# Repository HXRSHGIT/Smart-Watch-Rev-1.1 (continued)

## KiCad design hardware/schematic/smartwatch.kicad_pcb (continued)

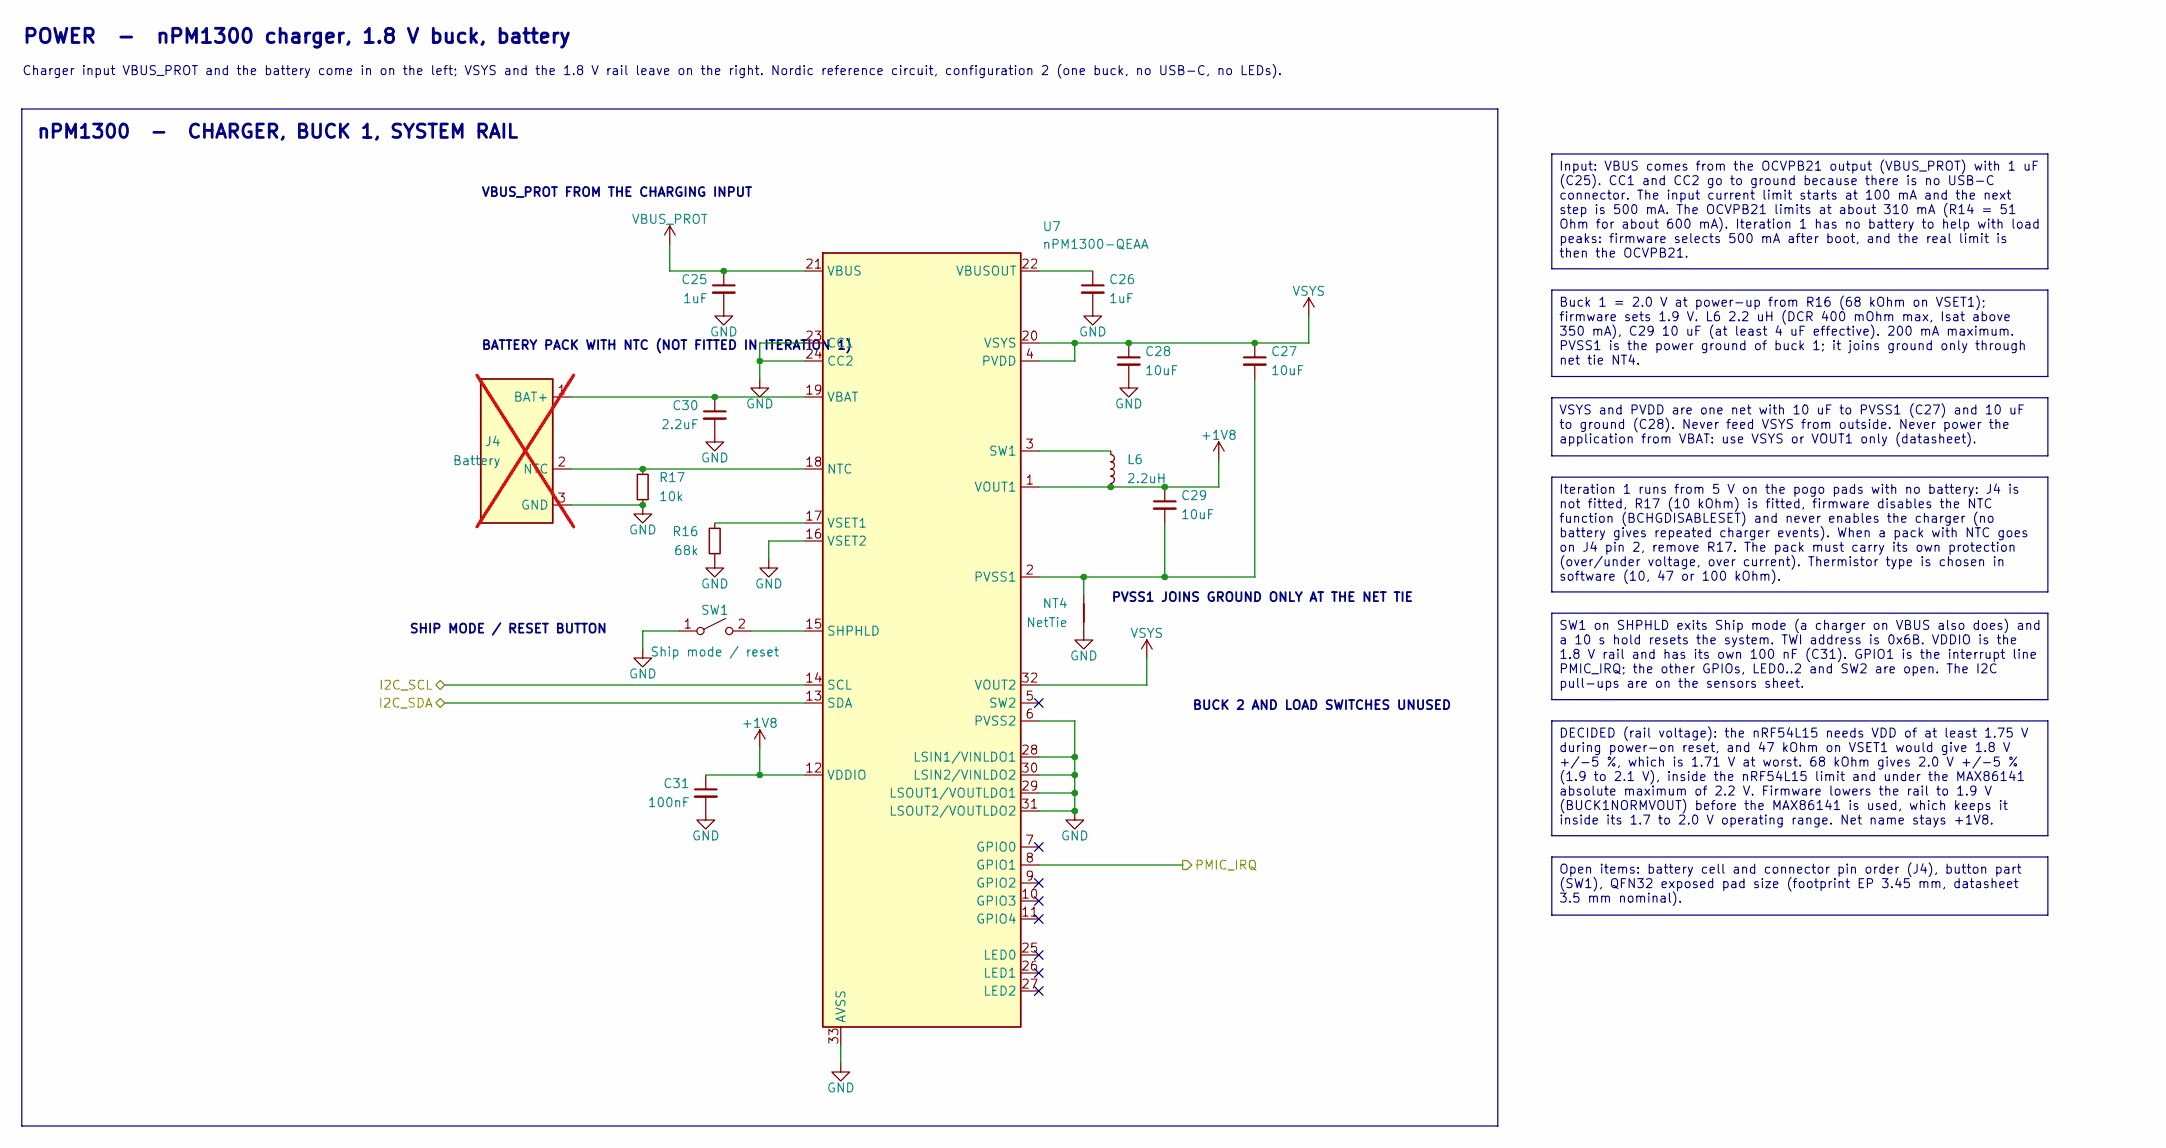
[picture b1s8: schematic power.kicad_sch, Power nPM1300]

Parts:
C25, C26: 1uF; C_0603_1608Metric
C27, C28, C29: 10uF; C_0603_1608Metric
C30: 2.2uF; C_0603_1608Metric
C31: 100nF; C_0201_0603Metric
J4: Battery; JST_SH_SM03B-SRSS-TB_1x03-1MP_P1.00mm_Horizontal; not fitted
L6: 2.2uH; L_0805_2012Metric
NT4: NetTie; NetTie-2_SMD_Pad0.5mm
R16: 68k; R_0201_0603Metric
R17: 10k; R_0201_0603Metric
SW1: Ship mode / reset; SW_SPST_B3U-1000P
U7: nPM1300-QEAA; QFN-32-1EP_5x5mm_P0.5mm_EP3.45x3.45mm

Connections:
+1V8: C29.1, C31.1, L6.2, U7.1 (VOUT1), U7.12 (VDDIO); also elsewhere on the board
/I2C_SCL: U7.14 (SCL); also elsewhere on the board
/I2C_SDA: U7.13 (SDA); also elsewhere on the board
/mcu/PMIC_IRQ: U7.8 (GPIO1); also elsewhere on the board
GND: C25.2, C26.2, C28.2, C30.2, C31.2, J4.3 (GND), NT4.1, R16.2, R17.2, SW1.1 (A), U7.6 (PVSS2), U7.16 (VSET2), U7.23 (CC1), U7.24 (CC2), U7.28 (LSIN1/VINLDO1), U7.29 (LSOUT1/VOUTLDO1), U7.30 (LSIN2/VINLDO2), U7.31 (LSOUT2/VOUTLDO2), U7.33 (AVSS); also elsewhere on the board
unnamed: C30.1, J4.1 (BAT+), U7.19 (VBAT)
unnamed: J4.2 (NTC), R17.1, U7.18 (NTC)
unnamed: SW1.2 (B), U7.15 (SHPHLD)
unnamed: C27.2, C29.2, NT4.2, U7.2 (PVSS1)
unnamed: L6.1, U7.3 (SW1)
unnamed: C26.1, U7.22 (VBUSOUT)
unnamed: R16.1, U7.17 (VSET1)
VBUS_PROT: C25.1, U7.21 (VBUS); also elsewhere on the board
VSYS: C27.1, C28.1, U7.4 (PVDD), U7.20 (VSYS), U7.32 (VOUT2); also elsewhere on the board

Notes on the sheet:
POWER - nPM1300 charger, 1.8 V buck, battery
Charger input VBUS_PROT and the battery come in on the left; VSYS and the 1.8 V rail leave on the right. Nordic reference circuit, configuration 2 (one buck, no USB-C, no LEDs).
nPM1300 - CHARGER, BUCK 1, SYSTEM RAIL
VBUS_PROT FROM THE CHARGING INPUT
BATTERY PACK WITH NTC (NOT FITTED IN ITERATION 1)
SHIP MODE / RESET BUTTON
PVSS1 JOINS GROUND ONLY AT THE NET TIE
BUCK 2 AND LOAD SWITCHES UNUSED
Input: VBUS comes from the OCVPB21 output (VBUS_PROT) with 1 uF (C25). CC1 and CC2 go to ground because there is no USB-C connector. The input current limit starts at 100 mA and the next step is 500 mA. The OCVPB21 limits at about 310 mA (R14 = 51 Ohm for about 600 mA). Iteration 1 has no battery t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
Buck 1 = 2.0 V at power-up from R16 (68 kOhm on VSET1); firmware sets 1.9 V. L6 2.2 uH (DCR 400 mOhm max, Isat above 350 mA), C29 10 uF (at least 4 uF effective). 200 mA maximum. PVSS1 is the power ground of buck 1; it joins ground only through net tie NT4.
VSYS and PVDD are one net with 10 uF to PVSS1 (C27) and 10 uF to ground (C28). Never feed VSYS from outside. Never power the application from VBAT: use VSYS or VOUT1 only (datasheet).
Iteration 1 runs from 5 V on the pogo pads with no battery: J4 is not fitted, R17 (10 kOhm) is fitted, firmware disables the NTC function (BCHGDISABLESET) and never enables the charger (no battery gives repeated charger events). When a pack with NTC goes on J4 pin 2, remove R17. The pack must carry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
SW1 on SHPHLD exits Ship mode (a charger on VBUS also does) and a 10 s hold resets the system. TWI address is 0x6B. VDDIO is the 1.8 V rail and has its own 100 nF (C31). GPIO1 is the interrupt line PMIC_IRQ; the other GPIOs, LED0..2 and SW2 are open. The I2C pull-ups are on the sensors sheet.
DECIDED (rail voltage): the nRF54L15 needs VDD of at least 1.75 V during power-on reset, and 47 kOhm on VSET1 would give 1.8 V +/-5 %, which is 1.71 V at worst. 68 kOhm gives 2.0 V +/-5 % (1.9 to 2.1 V), inside the nRF54L15 limit and under the MAX86141 absolute maximum of 2.2 V. Firmware lowers the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
Open items: battery cell and connector pin order (J4), button part (SW1), QFN32 exposed pad size (footprint EP 3.45 mm, datasheet 3.5 mm nominal).

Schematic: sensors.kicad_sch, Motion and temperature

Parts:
C19, C20, C21: 100nF; C_0201_0603Metric
R9, R10: 4.7k; R_0201_0603Metric
TP6: TP I2C_SDA; TestPoint_Pad_D1.0mm
TP7: TP I2C_SCL; TestPoint_Pad_D1.0mm
U3: BMI270; Bosch_LGA-14_3x2.5mm_P0.5mm
U4: MAX30208; MAX30208_TLGA-10_2x2mm

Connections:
+1V8: C19.1, C20.1, C21.1, R9.1, R10.1, U3.2 (ASDx), U3.3 (ASCx), U3.5 (VDDIO), U3.8 (VDD), U3.12 (CSB), U4.1 (VDD), U4.2 (VDD), U4.3 (VDD); also elsewhere on the board
/I2C_SCL: R9.2, TP7.1, U3.13 (SCx (SCL)), U4.9 (SCL); also elsewhere on the board
/I2C_SDA: R10.2, TP6.1, U3.14 (SDx (SDA)), U4.8 (SDA); also elsewhere on the board
/mcu/IMU_INT1: U3.4 (INT1); also elsewhere on the board
/mcu/IMU_INT2: U3.9 (INT2); also elsewhere on the board
/mcu/TEMP_INT: U4.10 (GPIO0); also elsewhere on the board
GND: C19.2, C20.2, C21.2, U3.1 (SDO), U3.6 (GNDIO), U3.7 (GND), U4.4 (GND), U4.5 (GND), U4.6 (GND), U4.7 (GPIO1); also elsewhere on the board

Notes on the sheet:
MOTION AND SKIN TEMPERATURE - BMI270 + MAX30208 on the I2C bus
Both parts run from the 1.8 V rail and share SDA / SCL. Interrupts go to the processor.
BMI270 - MOTION
I2C PULL-UPS
MAX30208 - SKIN TEMPERATURE
BMI270: I2C address 0x68 because SDO is tied to ground. CSB high selects I2C. ASDx and ASCx (the secondary interface) are tied to VDDIO as the datasheet requires, never to ground. OCSB and OSDO are not used.
C19 and C20 are decoupling capacitors for BMI270 VDD and VDDIO (100 nF each). Keep them close to the pins.
MAX30208: address 0x50. GPIO1 is tied to ground, and GPIO0 reads low at start-up through its internal 1 MOhm pull-down, so the address stays 0x50. GPIO0 is the temperature alarm output (TEMP_INT), open drain and active low in INTB mode: set that mode first, then enable the processor's internal pull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
C21 decouples MAX30208 VDD (100 nF). Keep it close to the pins. Read PCN 2204 before ordering.
One pair of 4.7 kOhm pull-ups serves the whole bus. At 400 kHz and about 50 pF the rise time is about 0.2 us. The nPM1300 joins this bus on the power sheet.

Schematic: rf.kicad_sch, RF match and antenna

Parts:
AE1: 2450AT18A0100001E; Johanson_2450AT18A0100001E_1206
C6: 1.5pF; C_0201_0603Metric; MPN GJM0335C1E1R5WB01
C9: 2.0pF; C_0201_0603Metric; MPN GJM0335C1E2R0WB01
C11: 0.3pF; C_0201_0603Metric
C14: TBD; C_0402_1005Metric; not fitted
L2: 2.7nH; L_0201_0603Metric; MPN LQP03HQ2N7B02
L3, L4: 3.5nH; L_0201_0603Metric; MPN LQP03HQ3N5B02
NT2: NetTie; NetTie-2_SMD_Pad0.5mm
R2, R3: 0R; R_0402_1005Metric

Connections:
/mcu/RF_ANT: L2.1; also elsewhere on the board
/mcu/VSS_PA: C6.2; also elsewhere on the board
GND: C11.2, C14.2, NT2.1; also elsewhere on the board
unnamed: AE1.1 (FEED), R3.2
unnamed: C6.1, L2.2, L3.1
unnamed: C9.1, L3.2, L4.1
unnamed: C9.2, NT2.2
unnamed: C11.1, L4.2, R2.1
unnamed: C14.1, R2.2, R3.1

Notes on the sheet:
RF - Nordic match network, antenna tee, chip antenna
The signal runs left to right: ANT pin of the processor, series-shunt-series filter, tee slots, antenna.
NORDIC FILTER AND MATCH
ANTENNA TEE AND ANTENNA
BOTTOM GND ONLY
Nordic network: C6 returns to VSS_PA on the TOP layer only. C9 returns to the BOTTOM ground layer only (net tie NT2). Place the whole network as close to the ANT pin as possible. (nRF54L15 datasheet, Fig 180 and Table 87)
Antenna tee: 0R, empty, 0R as a start (R2, C14, R3). The antenna is the Johanson 2450AT18A0100001E in a corner with its keep-out. Tune on the worn band with the final housing. Pin 2 is only a solder anchor. Johanson's own evaluation board uses series 1.0 pF, shunt 2.7 nH, series 3.9 nH: the shunt s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

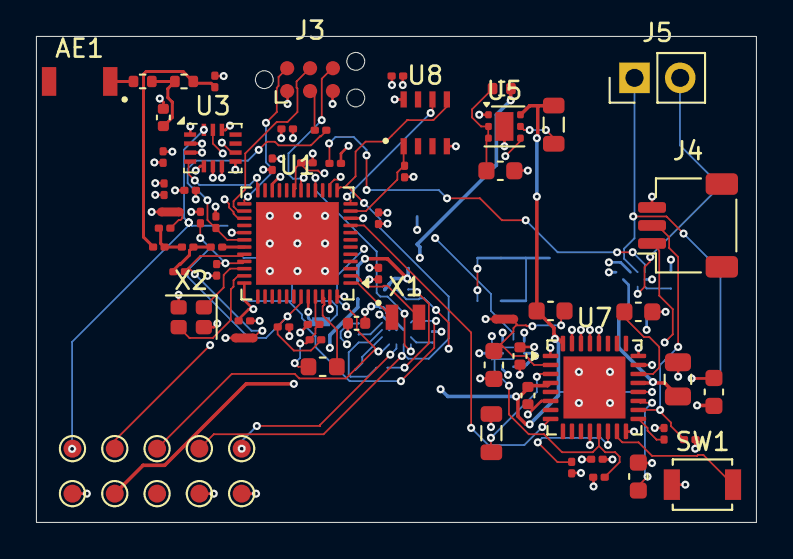
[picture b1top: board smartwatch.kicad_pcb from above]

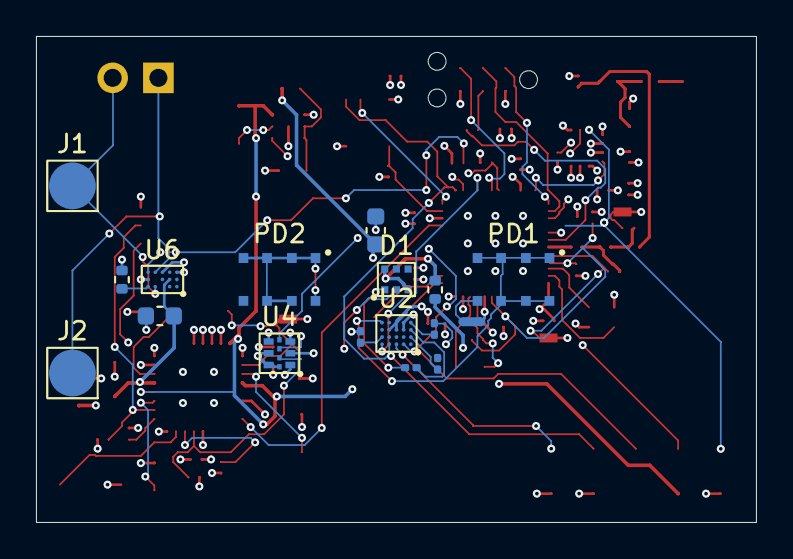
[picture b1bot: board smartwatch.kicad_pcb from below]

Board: 4 copper layers, 40.0 x 27.0 mm, 89 parts (17 on the bottom side), 60 nets.

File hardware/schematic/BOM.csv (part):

Reference,Value,Footprint,Spec,MPN,Source,Note
AE1,2450AT18A0100001E,smartwatch:Johanson_2450AT18A0100001E_1206,,,Johanson DS 36S0021A rev 4.0,
C1,2.2uF,Capacitor_SMD:C_0201_0603Metric,X6T 20% 2.5V,,nRF54L15 DS v1.0 Table 87 / Fig 180,
C2,2.2uF,Capacitor_SMD:C_0201_0603Metric,X6T 20% 2.5V,,nRF54L15 DS v1.0 Table 87 / Fig 180,
C3,10uF,Capacitor_SMD:C_0402_1005Metric,X6S 20% 6.3V,,nRF54L15 DS v1.0 Table 87 / Fig 180,
C4,100nF,Capacitor_SMD:C_0201_0603Metric,X7R 10%,,nRF54L15 DS v1.0 Table 87 / Fig 180,
C5,2.2nF,Capacitor_SMD:C_0201_0603Metric,X7R 10% 10V,,nRF54L15 DS v1.0 Table 87 / Fig 180,
C6,1.5pF,Capacitor_SMD:C_0201_0603Metric,NP0 0.05 pF 25V high Q,GJM0335C1E1R5WB01,nRF54L15 DS v1.0 Fig 180 / Table 87,
C7,100nF,Capacitor_SMD:C_0201_0603Metric,X7R 10%,,nRF54L15 DS v1.0 Table 87 / Fig 180,
C8,100nF,Capacitor_SMD:C_0201_0603Metric,X7R 10%,,nRF54L15 DS v1.0 Table 87 / Fig 180,
C9,2.0pF,Capacitor_SMD:C_0201_0603Metric,NP0 0.05 pF 25V,GJM0335C1E2R0WB01,nRF54L15 DS v1.0 Fig 180 / Table 87,
C10,100nF,Capacitor_SMD:C_0201_0603Metric,X7R 10%,,nRF54L15 DS v1.0 Table 87 / Fig 180,
C11,0.3pF,Capacitor_SMD:C_0201_0603Metric,C0G 0.1 pF 50V,,nRF54L15 DS v1.0 Fig 180 / Table 87,
C12,10nF,Capacitor_SMD:C_0201_0603Metric,X7R 6.3V,,nRF54L15 DS v1.0 Table 87 / Fig 180,
C13,3.9pF,Capacitor_SMD:C_0201_0603Metric,C0G 0.25pF 50V,,nRF54L15 DS v1.0 Table 87 / Fig 180,
C14,TBD,Capacitor_SMD:C_0402_1005Metric,"shunt slot, tune on worn band",,Johanson DS 36S0021A note 4,DNP
C15,22uF,Capacitor_SMD:C_0402_1005Metric,"6.3V or higher, effective ~10 uF",,MAX86141 DS Rev 5 p.49,
C16,100nF,Capacitor_SMD:C_0201_0603Metric,at the VDD_ANA ball,,MAX86141 DS Rev 5 p.12,
C17,1uF,Capacitor_SMD:C_0201_0603Metric,6.3V (VREF is 1.21 V),,MAX86141 DS Rev 5 p.12,
C18,10uF,Capacitor_SMD:C_0603_1608Metric,10V X5R (VLED up to 5.5 V),,MAX86141 DS Rev 5 p.12,
C19,100nF,Capacitor_SMD:C_0201_0603Metric,X7R 10%,,BMI270 DS Rev 08 section 7.2,
C20,100nF,Capacitor_SMD:C_0201_0603Metric,X7R 10%,,BMI270 DS Rev 08 section 7.2,
C21,100nF,Capacitor_SMD:C_0201_0603Metric,X7R 10%,,MAX30208 DS Rev 1 p.5 pin table,
C22,2.2uF,Capacitor_SMD:C_0402_1005Metric,X5R 6.3V min,,TPS61240 DS SLVS806D Table 2,
C23,10uF,Capacitor_SMD:C_0603_1608Metric,X5R 10V (effective >= 2.7 uF at 5 V),,TPS61240 DS SLVS806D 10.2.2.4,
C24,22uF,Capacitor_SMD:C_0805_2012Metric,"X5R 16V low ESR, >= 10 uF effective at 5 V",,OCVPB21-13F6 DS13107 Rev 3 Table 2,
C25,1uF,Capacitor_SMD:C_0603_1608Metric,X5R 10V 10%,,"nPM1300 PS v1.3 Reference circuitry, Configuration 2 C1",
C26,1uF,Capacitor_SMD:C_0603_1608Metric,"X5R 10V 10%, mandatory on VBUSOUT",,"nPM1300 PS v1.3 Reference circuitry, Configuration 2 C5",
C27,10uF,Capacitor_SMD:C_0603_1608Metric,"X5R 25V 20%, returns to PVSS1",,"nPM1300 PS v1.3 Reference circuitry, Configuration 2 C2",
C28,10uF,Capacitor_SMD:C_0603_1608Metric,X5R 25V 20%,,"nPM1300 PS v1.3 Reference circuitry, Configuration 2 C4",
C29,10uF,Capacitor_SMD:C_0603_1608Metric,X5R 25V 20% (>= 4 uF effective),,"nPM1300 PS v1.3 Reference circuitry, Configuration 2 C7",
C30,2.2uF,Capacitor_SMD:C_0603_1608Metric,X7R 16V 10%,,"nPM1300 PS v1.3 Reference circuitry, Configuration 2 C6",
C31,100nF,Capacitor_SMD:C_0201_0603Metric,X5R 10%,,"nPM1300 PS v1.3 Reference circuitry, Configuration 2 C13",
C32,100nF,Capacitor_SMD:C_0201_0603Metric,"X7R 10%, close to the VCC land",,MX25R3235F DS rev 1.6 section 12,
D1,SFH 7016,smartwatch:SFH7016_1.85x1.65mm,,,,
FB1,120R@100MHz,Inductor_SMD:L_0201_0603Metric,200 mA 500 mOhm max,,nRF54L15 DS v1.0 Table 87 / Fig 180,
J1,Pogo pad,smartwatch:Pogo_Pad_D2.6mm,,,research/power-battery/POGO_CHARGING.md,
J2,Pogo pad,smartwatch:Pogo_Pad_D2.6mm,,,research/power-battery/POGO_CHARGING.md,
J3,TC2030-NL,Connector:Tag-Connect_TC2030-IDC-NL_2x03_P1.27mm_Vertical,,,,
J4,Battery,Connector_JST:JST_SH_SM03B-SRSS-TB_1x03-1MP_P1.00mm_Horizontal,not fitted in iteration 1 (no battery),,battery cell and connector: open item,
J5,5 V in,Connector_PinHeader_2.54mm:PinHeader_1x02_P2.54mm_Vertical,,,iteration 1: 5 V input without pogo contact,
L1,4.7uH,Inductor_SMD:L_0603_1608Metric,120 mA 20% 650 mOhm,,nRF54L15 DS v1.0 Table 87 / Fig 180,
L2,2.7nH,Inductor_SMD:L_0201_0603Metric,0.1 nH 600 mA,LQP03HQ2N7B02,nRF54L15 DS v1.0 Fig 180 / Table 87,
L3,3.5nH,Inductor_SMD:L_0201_0603Metric,0.1 nH 500 mA,LQP03HQ3N5B02,nRF54L15 DS v1.0 Fig 180 / Table 87,
L4,3.5nH,Inductor_SMD:L_0201_0603Metric,0.1 nH 500 mA,LQP03HQ3N5B02,nRF54L15 DS v1.0 Fig 180 / Table 87,
L5,1.0uH,Inductor_SMD:L_0805_2012Metric,"1.0 uH min, Isat > 0.9 A",LQM21PN1R0MC0,TPS61240 DS SLVS806D Table 2/3,
L6,2.2uH,Inductor_SMD:L_0805_2012Metric,"DCR <= 400 mOhm, Isat > 350 mA, 20%",,nPM1300 PS v1.3 BUCK component selection,
NT1,NetTie,NetTie:NetTie-2_SMD_Pad0.5mm,,,nRF54L15 DS v1.0 Table 87 / Fig 180 note on C6,
NT2,NetTie,NetTie:NetTie-2_SMD_Pad0.5mm,,,nRF54L15 DS v1.0 Fig 180 / Table 87 note on C9,
NT3,NetTie,NetTie:NetTie-2_SMD_Pad0.5mm,,,MAX86141 DS Rev 5 layout guidelines p.49: PD_GND to ground at one point,
NT4,NetTie,NetTie:NetTie-2_SMD_Pad0.5mm,,,"nPM1300 PS v1.3 Reference circuitry, Configuration 2 (net tie on PVSS1)",
PD1,VEMD8080,smartwatch:VEMD8080_4.8x2.5mm,,,,
PD2,VEMD8080,smartwatch:VEMD8080_4.8x2.5mm,,,,
R1,1k,Resistor_SMD:R_0201_0603Metric,1% 0.05W,,nRF54L15 DS v1.0 Table 87 / Fig 180,
R2,0R,Resistor_SMD:R_0402_1005Metric,series slot,,Johanson DS 36S0021A note 4,
R3,0R,Resistor_SMD:R_0402_1005Metric,series slot,,Johanson DS 36S0021A note 4,
R6,0R,Resistor_SMD:R_0201_0603Metric,link,,bring-up current measurement,
R7,0R,Resistor_SMD:R_0201_0603Metric,link,,bring-up current measurement,
R8,0R,Resistor_SMD:R_0201_0603Metric,link,,bring-up current measurement,
R9,4.7k,Resistor_SMD:R_0201_0603Metric,pull-up,,"I2C 400 kHz, 50 pF -> rise time about 0.2 us",
R10,4.7k,Resistor_SMD:R_0201_0603Metric,pull-up,,"I2C 400 kHz, 50 pF -> rise time about 0.2 us",
R11,100k,Resistor_SMD:R_0201_0603Metric,pull-down,,nRF54L15 errata 103,
R12,0R,Resistor_SMD:R_0402_1005Metric,"VLED from the boost (default, fitted)",,power tree option B,
R13,0R,Resistor_SMD:R_0402_1005Metric,"VLED straight from VSYS (DNP, power tree option A)",,power tree option A,DNP
R14,180R,Resistor_SMD:R_0402_1005Metric,"1% or better, 51-270 Ohm allowed",,OCVPB21-13F6 DS13107 Rev 3 section 1.2,
R15,100k,Resistor_SMD:R_0201_0603Metric,FLAG pull-up,,OCVPB21-13F6 DS13107 Rev 3 Table 2,
R16,68k,Resistor_SMD:R_0201_0603Metric,"1% (sets BUCK1 = 2.0 V at power-up, firmware sets 1.9 V)",,nPM1300 PS v1.3 BUCK output voltage selection,
R17,10k,Resistor_SMD:R_0201_0603Metric,NTC substitute: fitted while J4 is empty (iteration 1); remove when a pack WITH thermistor goes on J4,,nPM1300 PS v1.3 NTC thermistor configuration,
R18,100k,Resistor_SMD:R_0201_0603Metric,CS# pull-up,,MX25R3235F DS rev 1.6 power-on state; nRF54L15 errata 103,
SW1,Ship mode / reset,Button_Switch_SMD:SW_SPST_B3U-1000P,,,nPM1300 PS v1.3 Ship and Hibernate modes,
TP1,TP +1V8,TestPoint:TestPoint_Pad_D1.0mm,,,,
TP2,TP VSYS,TestPoint:TestPoint_Pad_D1.0mm,,,,
TP3,TP VLED,TestPoint:TestPoint_Pad_D1.0mm,,,,
TP4,TP GND,TestPoint:TestPoint_Pad_D1.0mm,,,,
TP5,TP GND,TestPoint:TestPoint_Pad_D1.0mm,,,,
TP6,TP I2C_SDA,TestPoint:TestPoint_Pad_D1.0mm,,,,
TP7,TP I2C_SCL,TestPoint:TestPoint_Pad_D1.0mm,,,,
TP8,TP SPI_SCK,TestPoint:TestPoint_Pad_D1.0mm,,,,
TP9,TP SPI_MOSI,TestPoint:TestPoint_Pad_D1.0mm,,,,
TP10,TP SPI_MISO,TestPoint:TestPoint_Pad_D1.0mm,,,,
U1,nRF54L15-QFAA,Package_DFN_QFN:QFN-48-1EP_6x6mm_P0.4mm_EP4.6x4.6mm,,,,
U2,MAX86141ENP+,smartwatch:MAX86141_WLP-20_2.048x1.848mm_P0.4mm,,,,
U3,BMI270,Package_LGA:Bosch_LGA-14_3x2.5mm_P0.5mm,,,,
U4,MAX30208,smartwatch:MAX30208_TLGA-10_2x2mm,,,,
U5,TPS61240DRVR,Package_SON:WSON-6-1EP_2x2mm_P0.65mm_EP1x1.6mm,,,,
U6,OCVPB21-13F6,smartwatch:OCVPB21-13F6_WLCSP-13_P0.4mm,,,,
U7,nPM1300-QEAA,Package_DFN_QFN:QFN-32-1EP_5x5mm_P0.5mm_EP3.45x3.45mm,,,,
U8,MX25R3235FZBIL0,smartwatch:MX25R3235F_USON-8_4x3mm_P0.8mm,,,,
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
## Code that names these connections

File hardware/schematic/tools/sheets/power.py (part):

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    d.caption("SHIP MODE / RESET BUTTON", (lx - 44) * U, sh[1] + 0.5 * U, size=1.27)

    # I2C: straight to the sheet ports
    for pin, name in (("14", "I2C_SCL"), ("13", "I2C_SDA")):
        x, y = L(pin)
        d.w((x, y), ((lx - 40) * U, y))
        d.port(name, (lx - 40) * U, y, "L", "bidirectional")
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    d.w(((lx - 11) * U, vi[1]), c31.p(1))
    d.gnd(*c31.p(2))

    # ============================================================ RIGHT: VBUSOUT, VSYS, buck 1, unused pins
    # VBUSOUT: decoupling only
    vo = L("22")
    c26 = part(d, "C", "C26", "1uF", "0603", rx + 6, Y("22") + 2, "X5R 10V 10%, mandatory on VBUSOUT", CFG2 + " C5")
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    d.gnd(*bot)
    d.caption("PVSS1 JOINS GROUND ONLY AT THE NET TIE", (rx + 8) * U, pvss1[1] + 3 * U, size=1.27)

    # buck 2 unused: VOUT2 to VSYS, SW2 open, PVSS2 and the four load-switch pins to ground
    v2o = L("32")
    d.w(v2o, ((rx + 12) * U, v2o[1]))
    d.w(((rx + 12) * U, v2o[1]), ((rx + 12) * U, v2o[1] - 3 * U))
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    d.gnd(gx, pins[-1][1])
    d.caption("BUCK 2 AND LOAD SWITCHES UNUSED", (rx + 17) * U, v2o[1] + 3 * U, size=1.27)

    # GPIO: GPIO1 is the interrupt output, the rest are open
    for pin in ("7", "9", "10", "11"):
        d.nc(*L(pin))
    g1 = L("8")
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                 "own protection (over/under voltage, over current). Thermistor type is chosen in software (10, 47 or 100 kOhm).",
              nx, 28 * U + h + h2 + h3 + 9, w)
    h5 = note(d, "SW1 on SHPHLD exits Ship mode (a charger on VBUS also does) and a 10 s hold resets the system. TWI "
                 "address is 0x6B. VDDIO is the 1.8 V rail and has its own 100 nF (C31). GPIO1 is the interrupt line "
                 "PMIC_IRQ; the other GPIOs, LED0..2 and SW2 are open. The I2C pull-ups are on the sensors sheet.",
              nx, 28 * U + h + h2 + h3 + h4 + 12, w)
    h6 = note(d, "DECIDED (rail voltage): the nRF54L15 needs VDD of at least 1.75 V during power-on reset, and 47 kOhm on "
                 "VSET1 would give 1.8 V +/-5 %, which is 1.71 V at worst. 68 kOhm gives 2.0 V +/-5 % (1.9 to 2.1 V), "
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
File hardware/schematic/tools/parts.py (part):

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    u = Unit("MAX86141 optical front end",
             top=[("A1", "VLED", PI), None, None, None, None, ("D2", "VDD_ANA", PI), ("C2", "VDD_DIG", PI)],
             bottom=[("D3", "PGND", PI), ("C4", "GND_ANA", PI), ("C3", "GND_DIG", PI)],
             left=[("B2", "INT", OD), None, None, None, None, ("B3", "GPIO1", BI), ("B4", "GPIO2", BI), None,
                   ("A5", "CSB", "input"), ("A2", "SCLK", "input"), ("A4", "SDI", "input"), ("A3", "SDO", TS)],
             right=[("D1", "LED1_DRV", PA), None, None, ("C1", "LED2_DRV", PA), None, None, ("B1", "LED3_DRV", PA)] + [None] * 7 + [
                    ("C5", "PD_GND", PA), ("D4", "PD2_IN", PA), ("D5", "PD1_IN", PA), None, ("B5", "VREF", PA)],
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    u = Unit("MAX30208 skin temperature",
             top=[("1", "VDD", PI), ("2", "VDD", PI), ("3", "VDD", PI)],
             bottom=[("4", "GND", PI), ("5", "GND", PI), ("6", "GND", PI)],
             left=[("8", "SDA", BI), ("9", "SCL", "input"), None, ("7", "GPIO1", "input")],
             right=[("10", "GPIO0", BI)], width=12.7)
    return chip_symbol("smartwatch", "MAX30208", "U", [u], footprint="smartwatch:MAX30208_TLGA-10_2x2mm",
                       datasheet=DS + "MAX30208.pdf", description="ADI MAX30208 digital temperature sensor, thin LGA-10.")

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    return chip_symbol("smartwatch", "TC2030_SWD", "J", [u],
                       footprint="Connector:Tag-Connect_TC2030-IDC-NL_2x03_P1.27mm_Vertical",
                       datasheet="Tag-Connect TC2030-CTX-NL cable (pin order per the TC2030-CTX drawing)",
                       description="Tag-Connect TC2030 no-legs SWD pads. Pin order: 1 VTREF, 2 SWDIO, 3 nRESET, 4 SWDCLK, 5 GND, 6 SWO.")

def npm1300():
    N = None
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                    ("32", "VOUT2", PA), ("5", "SW2", PA), ("6", "PVSS2", PA), N,
                    ("28", "LSIN1/VINLDO1", PA), ("30", "LSIN2/VINLDO2", PA), ("29", "LSOUT1/VOUTLDO1", PA),
                    ("31", "LSOUT2/VOUTLDO2", PA), N,
                    ("7", "GPIO0", BI), ("8", "GPIO1", BI), ("9", "GPIO2", BI), ("10", "GPIO3", BI), ("11", "GPIO4", BI), N,
                    ("25", "LED0", PA), ("26", "LED1", PA), ("27", "LED2", PA)],
             bottom=[("33", "AVSS", PI)], width=17.78)
    return chip_symbol("smartwatch", "nPM1300-QEAA", "U", [u], footprint="Package_DFN_QFN:QFN-32-1EP_5x5mm_P0.5mm_EP3.45x3.45mm",
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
